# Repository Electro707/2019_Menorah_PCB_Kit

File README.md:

# 2019_Menorah_PCB_Kit
A soldering kit in the shape of menorah powered by an ATtiny84

This repository is archived, as it's a one-time design.
Now files are hosted on Google Drive.

Link to website, in which the Google Drive link can be found:
[Link](https://electro707.com/documentation/PCB/2019_Menorah/index.php)

I may create a new general reposity for the kit that will be updated as time goes on 
(there also won't be any of the University of New Haven logos on that one).

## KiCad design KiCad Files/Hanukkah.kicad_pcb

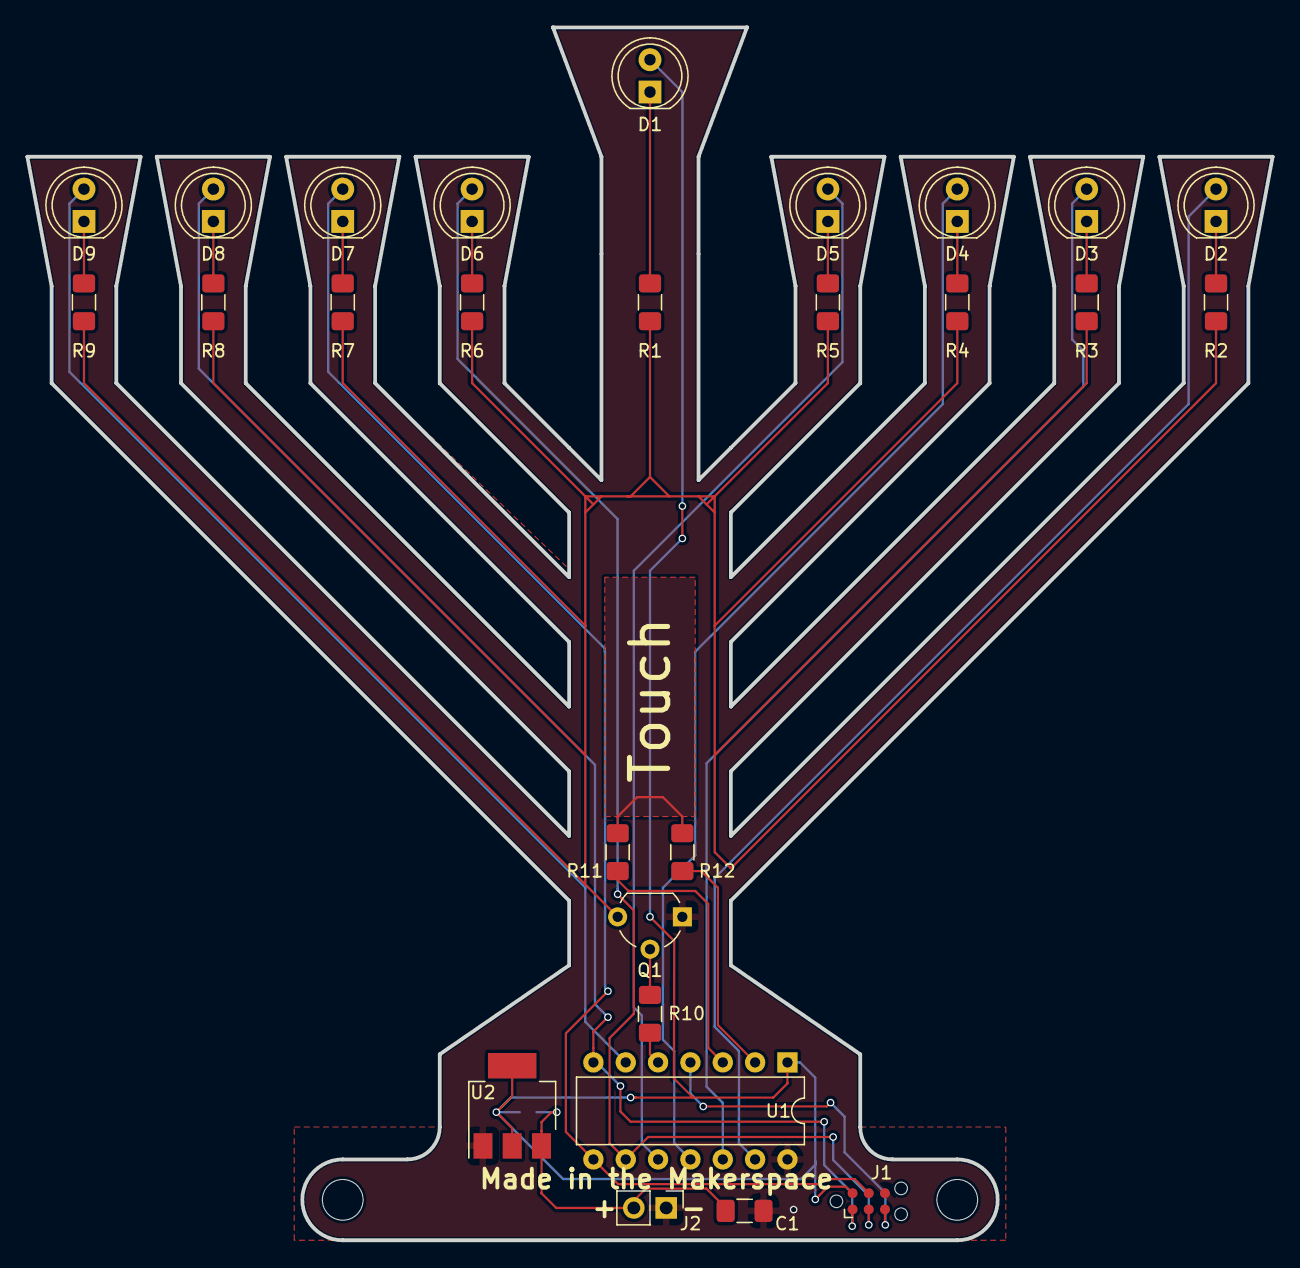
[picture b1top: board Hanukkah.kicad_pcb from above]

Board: 2 copper layers, 97.8 x 95.2 mm, 30 parts (1 on the bottom side), 27 nets.

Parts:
C1: 10uF; C_1206_3216Metric_Pad1.42x1.75mm_HandSolder
D1, D2, D3, D4, D5, D6, D7, D8, D9: LED_ALT; LED_D5.0mm
H1, H2: MountingHole; MountingHole_3.2mm_M3_DIN965
J1: Programming; Tag-Connect_TC2030-IDC-NL_2x03_P1.27mm_Vertical
J2: Conn_01x02; PinHeader_1x02_P2.54mm_Vertical
JP1: Jumper_2_Open; SolderJumper-2_P1.3mm_Open_RoundedPad1.0x1.5mm
Q1: 2N3904; TO-92_Wide
R1, R2, R3, R4, R5, R6, R7, R8, R9, R10, R11, R12: R; R_1206_3216Metric_Pad1.42x1.75mm_HandSolder
U1: ATtiny84-20PU; DIP-14_W7.62mm
U2: NCP1117-5.0_SOT223; SOT-223-3_TabPin2

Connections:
CopperPad: R11.1, R12.1
GND: C1.2, J1.6, J2.1, Q1.1, U1.14, U2.1
unnamed: C1.1, J2.2, JP1.1, U2.3
unnamed: D1.1, R1.1
unnamed: D2.1, R2.1
unnamed: D2.2, U1.13
unnamed: D3.1, R3.1
unnamed: D3.2, U1.12
unnamed: D4.1, R4.1
unnamed: D4.2, U1.11
unnamed: D5.1, R5.1
unnamed: D5.2, U1.10
unnamed: D6.1, R6.1
unnamed: D6.2, J1.3, U1.9
unnamed: D7.1, R7.1
unnamed: D7.2, J1.4, U1.8
unnamed: D8.1, R8.1
unnamed: D8.2, J1.1, U1.7
unnamed: D9.1, R9.1
unnamed: D9.2, U1.6
unnamed: J1.5, U1.4
unnamed: Q1.2, R10.2
unnamed: Q1.3, R1.2, R2.2, R3.2, R4.2, R5.2, R6.2, R7.2, R8.2, R9.2
unnamed: R10.1, U1.5
unnamed: R11.2, U1.3
unnamed: R12.2, U1.2
VCC: D1.2, J1.2, JP1.2, U1.1, U2.2

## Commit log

2020-04-16 Pre-Archive Change
